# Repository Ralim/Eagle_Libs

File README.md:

Eagle Libraries created/collected by RalimTek (Ben V. Brown)

Author : Ralim (ralim@ralimtek.com)

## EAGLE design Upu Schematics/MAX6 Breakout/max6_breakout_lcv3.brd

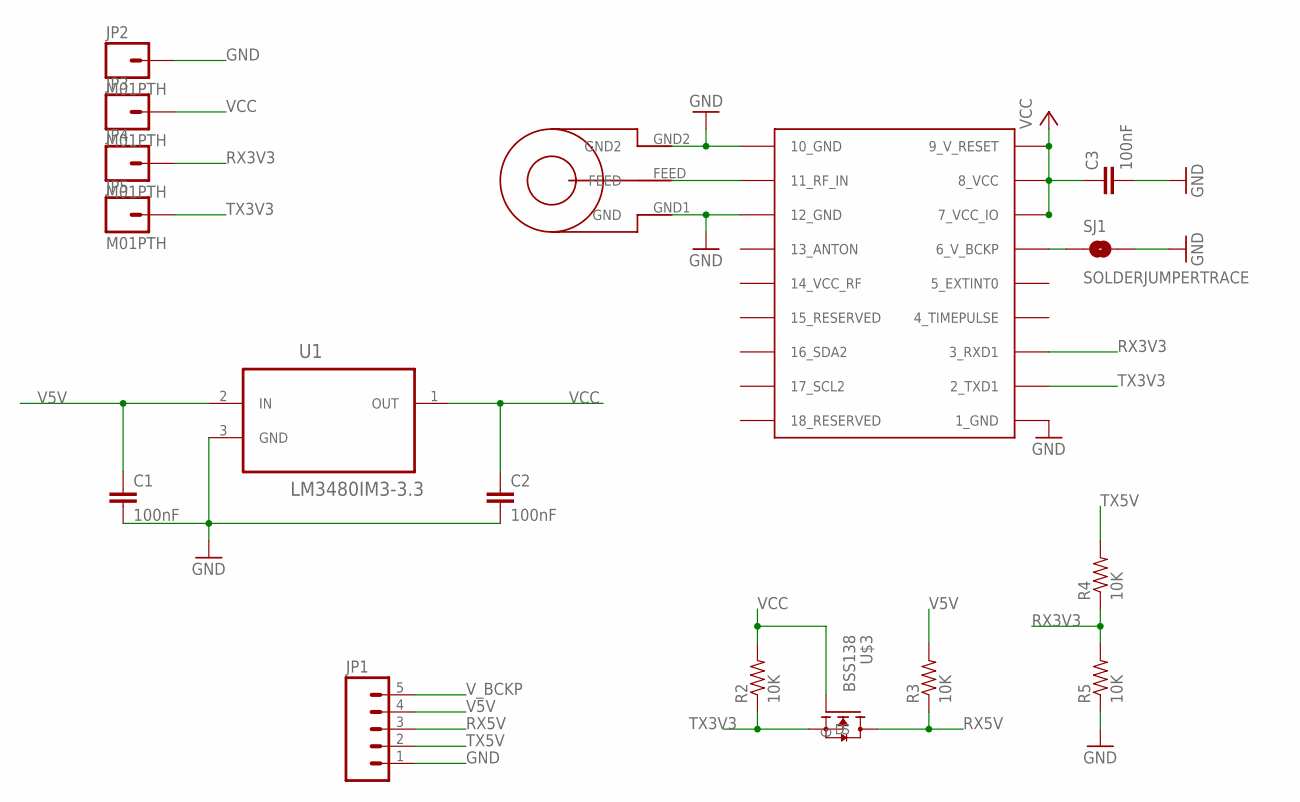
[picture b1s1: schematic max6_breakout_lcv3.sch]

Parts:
C1, C2, C3: 100nF; 0603-CAP
JP1: M05PTH; 1X05
JP2, JP3, JP4, JP5: M01PTH; 1X01
R2, R3, R4, R5: 10K; 0603-RES
SJ1: SOLDERJUMPERTRACE; SJ_2S-TRACE
U1: LM3480IM3-3.3; SOT95P251X112-3N
U$1: UBLOX_MAX-6
U$2: SARANTEL-SR1202
U$3: BSS138

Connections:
GND: C1.2, C2.2, C3.2, JP1.1, JP2.1, R5.1, SJ1.2, U1.3 (GND), U$1.1_GND, U$1.10_GND, U$1.12_GND, U$2.GND1 (GND), U$2.GND2
unnamed: U$1.11_RF_IN, U$2.FEED
RX3V3: JP4.1, R4.1, R5.2, U$1.3_RXD1
RX5V: JP1.3, R3.1, U$3.D
TX3V3: JP5.1, R2.1, U$1.2_TXD1, U$3.S
TX5V: JP1.2, R4.2
V5V: C1.1, JP1.4, R3.2, U1.2 (IN)
VCC: C2.1, C3.1, JP3.1, R2.2, U1.1 (OUT), U$1.7_VCC_IO, U$1.8_VCC, U$1.9_V_RESET, U$3.G
V_BCKP: JP1.5, SJ1.1, U$1.6_V_BCKP

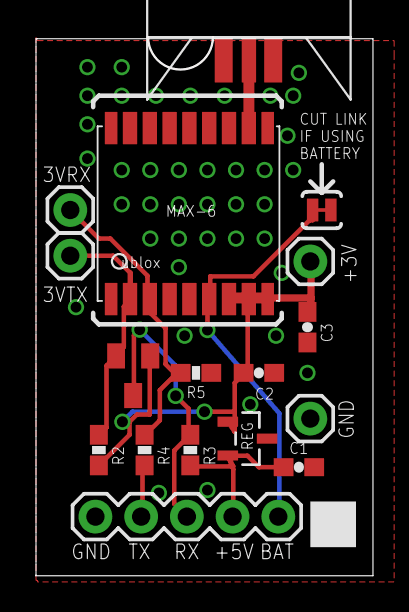
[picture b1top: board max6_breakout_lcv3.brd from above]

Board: 2 copper layers, 18.7 x 29.8 mm, 17 parts (0 on the bottom side), 9 nets.

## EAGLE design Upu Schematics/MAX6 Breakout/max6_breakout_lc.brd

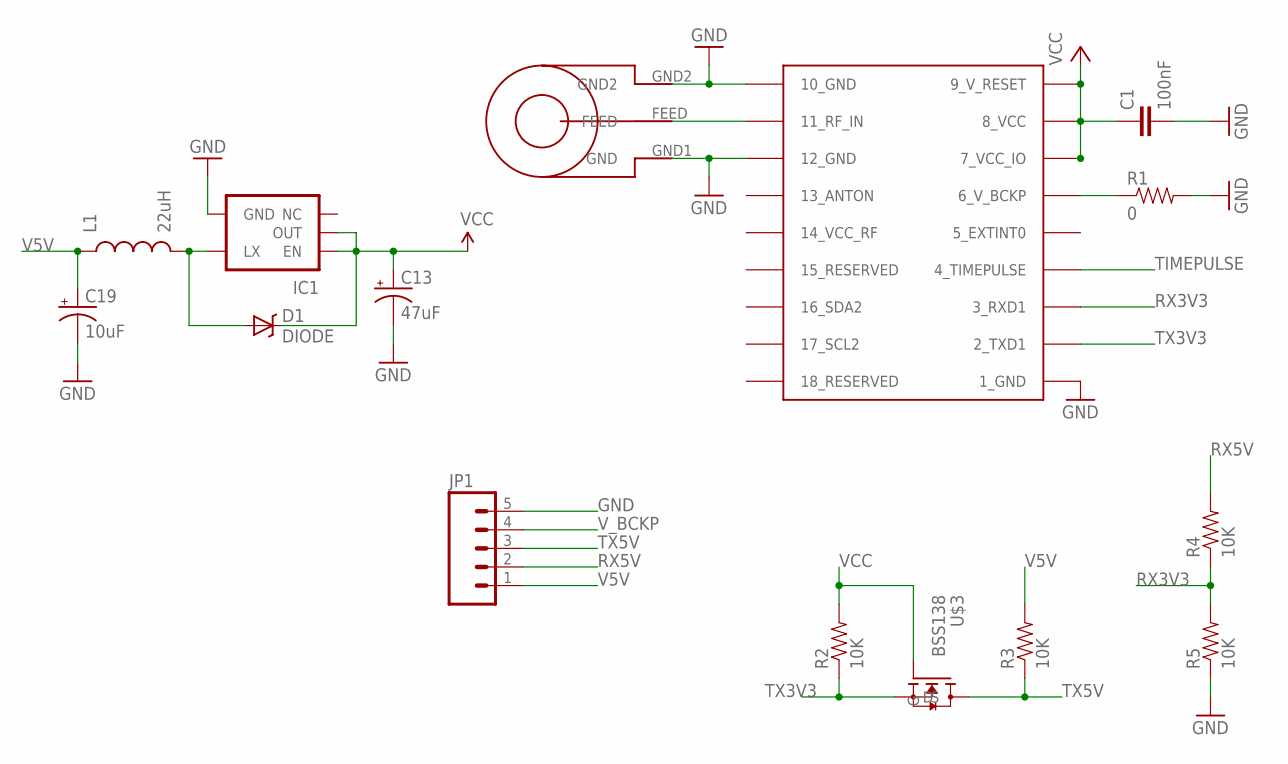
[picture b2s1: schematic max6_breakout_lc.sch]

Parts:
C1: 100nF; 0603-CAP
C13: 47uF; EIA3216
C19: 10uF; EIA3216
D1: DIODE; SMA-DIODE
IC1: V_REG_NCP1400SOT23-5; SOT23-5
JP1: M05PTH; 1X05
L1: 22uH; 1210
R1: 0; 0603-RES
R2, R3, R4, R5: 10K; 0603-RES
U$1: UBLOX_MAX-6
U$2: SARANTEL-SR1202
U$3: BSS138

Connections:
3.3V: C13.A (+), D1.C, IC1.1 (EN), IC1.2 (OUT)
GND: C1.2, C13.C (-), C19.C (-), IC1.4 (GND), JP1.5, R1.2, R5.1, U$1.1_GND, U$1.10_GND, U$1.12_GND, U$2.GND1 (GND), U$2.GND2
unnamed: U$1.11_RF_IN, U$2.FEED
unnamed: D1.A, IC1.5 (LX), L1.2
RX3V3: R4.1, R5.2, U$1.3_RXD1
RX5V: JP1.2, R4.2
TIMEPULSE: U$1.4_TIMEPULSE
TX3V3: R2.1, U$1.2_TXD1, U$3.S
TX5V: JP1.3, R3.1, U$3.D
V5V: C19.A (+), JP1.1, L1.1, R3.2
VCC: C1.1, R2.2, U$1.7_VCC_IO, U$1.8_VCC, U$1.9_V_RESET, U$3.G
V_BCKP: JP1.4, R1.1, U$1.6_V_BCKP

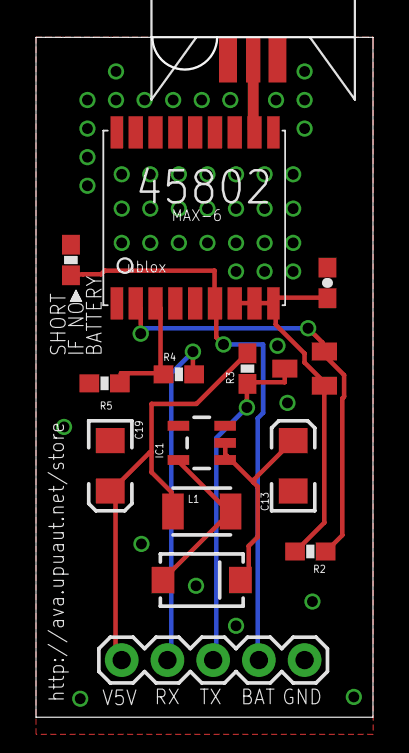
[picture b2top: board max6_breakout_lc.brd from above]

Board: 2 copper layers, 18.7 x 37.8 mm, 15 parts (0 on the bottom side), 11 nets.

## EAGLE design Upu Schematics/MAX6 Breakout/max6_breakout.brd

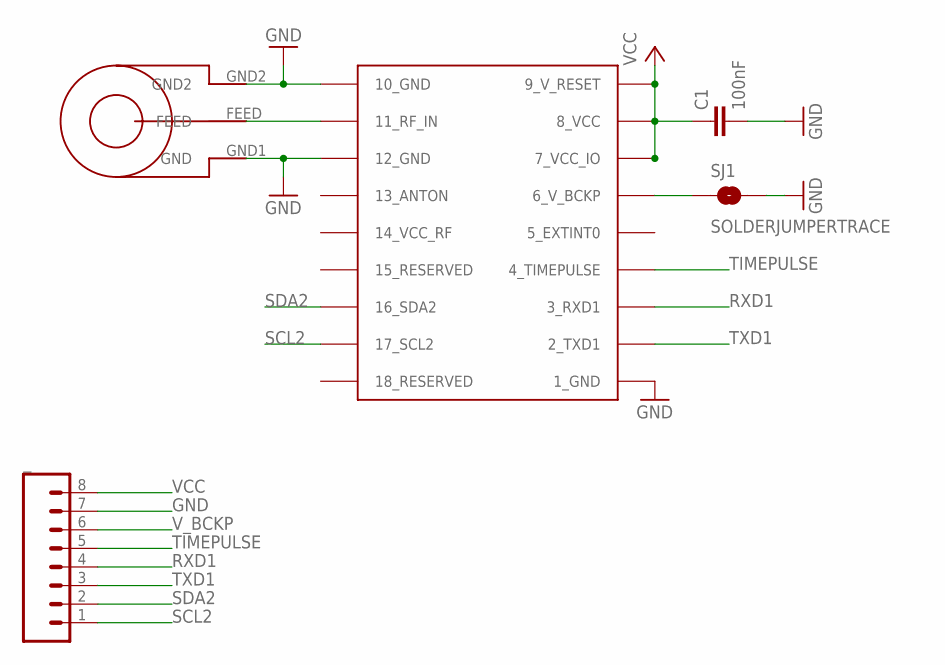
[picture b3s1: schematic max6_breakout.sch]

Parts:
C1: 100nF; 0603-CAP
SJ1: SOLDERJUMPERTRACE; SJ_2S-TRACE
U$1: UBLOX_MAX-6
U$2: SARANTEL-SR1202
_: M081X08; 1X08

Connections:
GND: C1.2, SJ1.2, U$1.1_GND, U$1.10_GND, U$1.12_GND, U$2.GND1 (GND), U$2.GND2, _.7
unnamed: U$1.11_RF_IN, U$2.FEED
RXD1: U$1.3_RXD1, _.4
SCL2: U$1.17_SCL2, _.1
SDA2: U$1.16_SDA2, _.2
TIMEPULSE: U$1.4_TIMEPULSE, _.5
TXD1: U$1.2_TXD1, _.3
VCC: C1.1, U$1.7_VCC_IO, U$1.8_VCC, U$1.9_V_RESET, _.8
V_BCKP: SJ1.1, U$1.6_V_BCKP, _.6

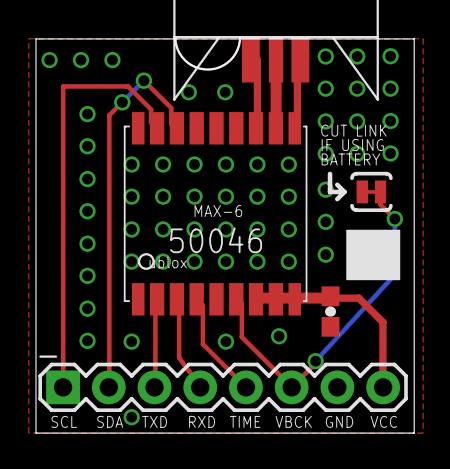
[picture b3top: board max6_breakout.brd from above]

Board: 2 copper layers, 21.0 x 21.9 mm, 5 parts (0 on the bottom side), 9 nets.

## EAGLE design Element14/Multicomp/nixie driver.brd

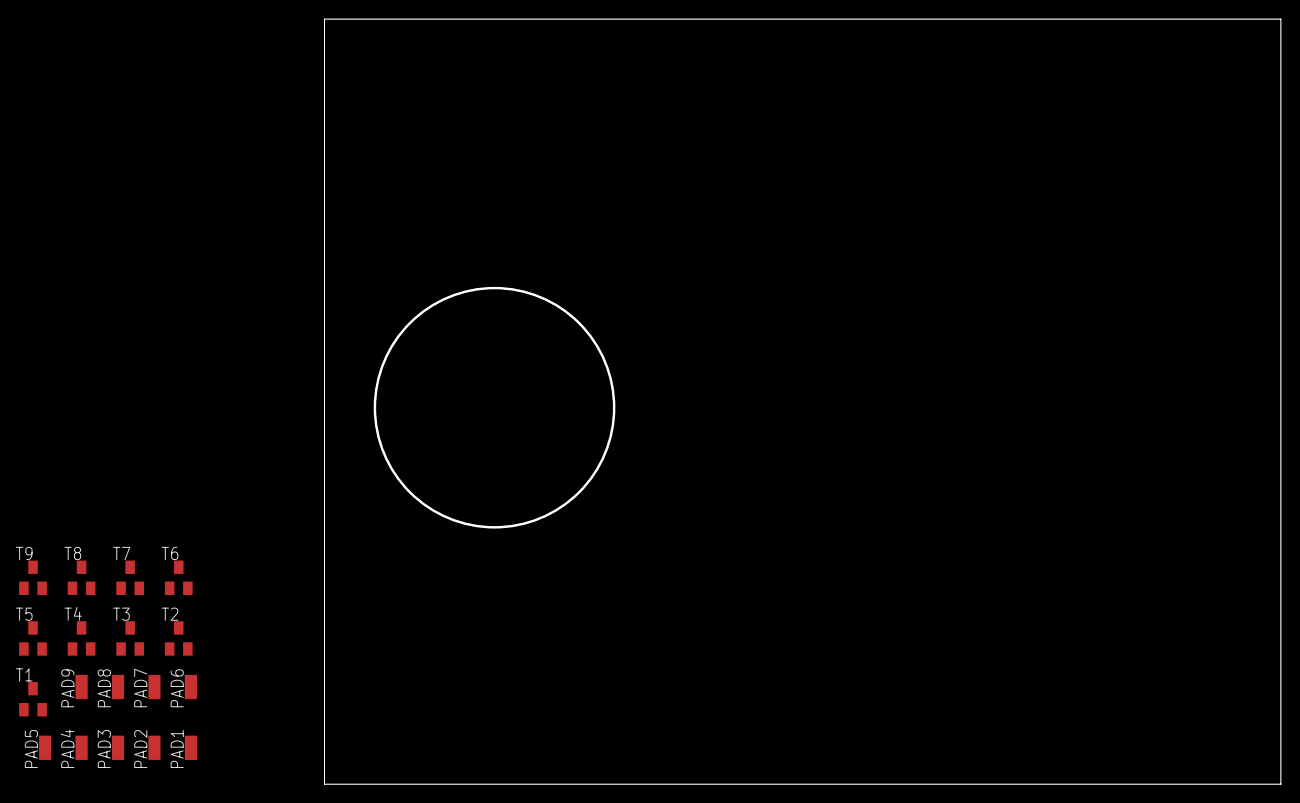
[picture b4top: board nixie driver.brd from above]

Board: 2 copper layers, 100.0 x 80.0 mm, 18 parts (0 on the bottom side), 10 nets, no tracks yet.

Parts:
PAD1, PAD2, PAD3, PAD4, PAD5, PAD6, PAD7, PAD8, PAD9: SMD1,27-2,54
T1, T2, T3, T4, T5, T6, T7, T8, T9: SOT23-BEC

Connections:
DGND: T1.E, T2.E, T3.E, T4.E, T5.E, T6.E, T7.E, T8.E, T9.E
unnamed: PAD5.1, T5.B
unnamed: PAD4.1, T4.B
unnamed: PAD3.1, T3.B
unnamed: PAD2.1, T2.B
unnamed: PAD1.1, T1.B
unnamed: PAD6.1, T6.B
unnamed: PAD7.1, T7.B
unnamed: PAD8.1, T8.B
unnamed: PAD9.1, T9.B

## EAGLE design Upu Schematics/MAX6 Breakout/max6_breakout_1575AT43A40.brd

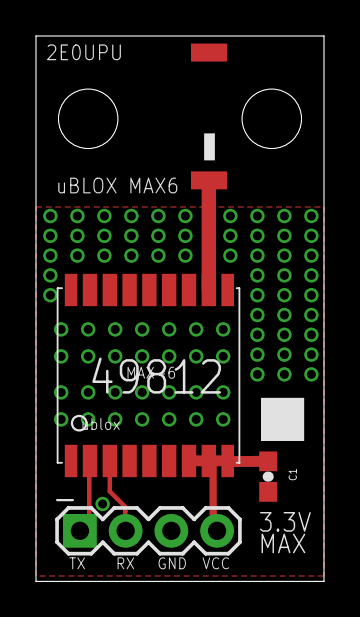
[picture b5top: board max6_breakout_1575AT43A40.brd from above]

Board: 2 copper layers, 16.0 x 30.3 mm, 6 parts (0 on the bottom side), 5 nets.

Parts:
C1: 100nF; 0603-CAP
JP1, JP2: STAND-OFF
U$1: UBLOX_MAX-6
U$2: JTI_ANTENNA-1575AT43A40
_: 1X04

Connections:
GND: C1.2, U$1.1_GND, U$1.6_V_BCKP, U$1.10_GND, U$1.12_GND, _.3
unnamed: U$1.11_RF_IN, U$2.FEED
RXD1: U$1.3_RXD1, _.2
TXD1: U$1.2_TXD1, _.1
VCC: C1.1, U$1.7_VCC_IO, U$1.8_VCC, U$1.9_V_RESET, _.4

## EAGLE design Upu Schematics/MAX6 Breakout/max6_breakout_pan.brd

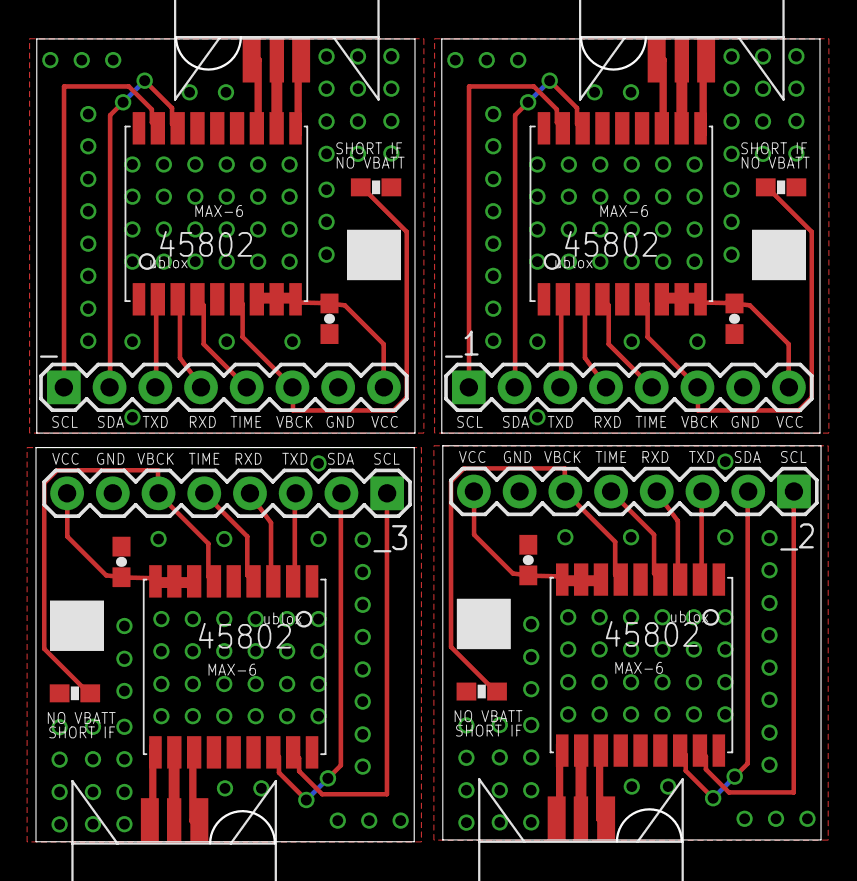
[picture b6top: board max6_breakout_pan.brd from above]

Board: 2 copper layers, 43.6 x 44.8 mm, 20 parts (0 on the bottom side), 36 nets.

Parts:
C1, C2, C3, C4: 100nF; 0603-CAP
R1, R2, R3, R4: 0; 0603-RES
U$1, U$3, U$5, U$7: UBLOX_MAX-6
U$2, U$4, U$6, U$8: SARANTEL-SR1202
_, _1, _2, _3: 1X08

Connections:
GND: C1.2, R1.2, U$1.1_GND, U$1.10_GND, U$1.12_GND, U$2.GND1, U$2.GND2, _.7
GND1: C2.2, R2.2, U$3.1_GND, U$3.10_GND, U$3.12_GND, U$4.GND1, U$4.GND2, _1.7
GND2: C3.2, R3.2, U$5.1_GND, U$5.10_GND, U$5.12_GND, U$6.GND1, U$6.GND2, _2.7
GND3: C4.2, R4.2, U$7.1_GND, U$7.10_GND, U$7.12_GND, U$8.GND1, U$8.GND2, _3.7
unnamed: U$3.11_RF_IN, U$4.FEED
unnamed: U$1.11_RF_IN, U$2.FEED
unnamed: U$5.11_RF_IN, U$6.FEED
unnamed: U$7.11_RF_IN, U$8.FEED
RXD1: U$1.3_RXD1, _.4
RXD2: U$3.3_RXD1, _1.4
RXD3: U$5.3_RXD1, _2.4
RXD4: U$7.3_RXD1, _3.4
SCL1: U$3.17_SCL2, _1.1
SCL2: U$1.17_SCL2, _.1
SCL3: U$5.17_SCL2, _2.1
SCL4: U$7.17_SCL2, _3.1
SDA1: U$3.16_SDA2, _1.2
SDA2: U$1.16_SDA2, _.2
SDA3: U$5.16_SDA2, _2.2
SDA4: U$7.16_SDA2, _3.2
TIMEPULSE: U$1.4_TIMEPULSE, _.5
TIMEPULSE1: U$3.4_TIMEPULSE, _1.5
TIMEPULSE2: U$5.4_TIMEPULSE, _2.5
TIMEPULSE3: U$7.4_TIMEPULSE, _3.5
TXD1: U$1.2_TXD1, _.3
TXD2: U$3.2_TXD1, _1.3
TXD3: U$5.2_TXD1, _2.3
TXD4: U$7.2_TXD1, _3.3
VCC: C1.1, U$1.7_VCC_IO, U$1.8_VCC, U$1.9_V_RESET, _.8
VCC1: C2.1, U$3.7_VCC_IO, U$3.8_VCC, U$3.9_V_RESET, _1.8
VCC2: C3.1, U$5.7_VCC_IO, U$5.8_VCC, U$5.9_V_RESET, _2.8
VCC3: C4.1, U$7.7_VCC_IO, U$7.8_VCC, U$7.9_V_RESET, _3.8
V_BCKP: R1.1, U$1.6_V_BCKP, _.6
V_BCKP1: R2.1, U$3.6_V_BCKP, _1.6
V_BCKP2: R3.1, U$5.6_V_BCKP, _2.6
V_BCKP3: R4.1, U$7.6_V_BCKP, _3.6

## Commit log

2014-04-19 Init
2014-04-29 Add new parts
    Add new parts including 9001 Digital Audio Decoder
    and Fangerous Prototypes Library
2014-05-12 Update
    +dirtypcbs files
    +DS18B20
    +update ralimtek lib
2014-05-12 organise
    Move files
2014-07-31 Update RalimtekLibs +tc2050 parts +tag connect parts
2014-07-31 +Merge library
2015-03-16 Cleanup, Add VFD Tubes
2015-03-16 +Update git ignore
2015-05-05 +cleanup
2015-05-05 Add atmel ATUC64L4U
2016-05-12 Add MCU's
2016-07-07 Sync public
2016-07-28 Add library for BQ7620 / BQ7630
2016-08-01 Fix BQ769x0 Collect DRV8412

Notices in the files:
parts and their libraries:
SparkFun: Licensing: CC v3.0 Share-Alike You are welcome to use this library for commercial purposes.
